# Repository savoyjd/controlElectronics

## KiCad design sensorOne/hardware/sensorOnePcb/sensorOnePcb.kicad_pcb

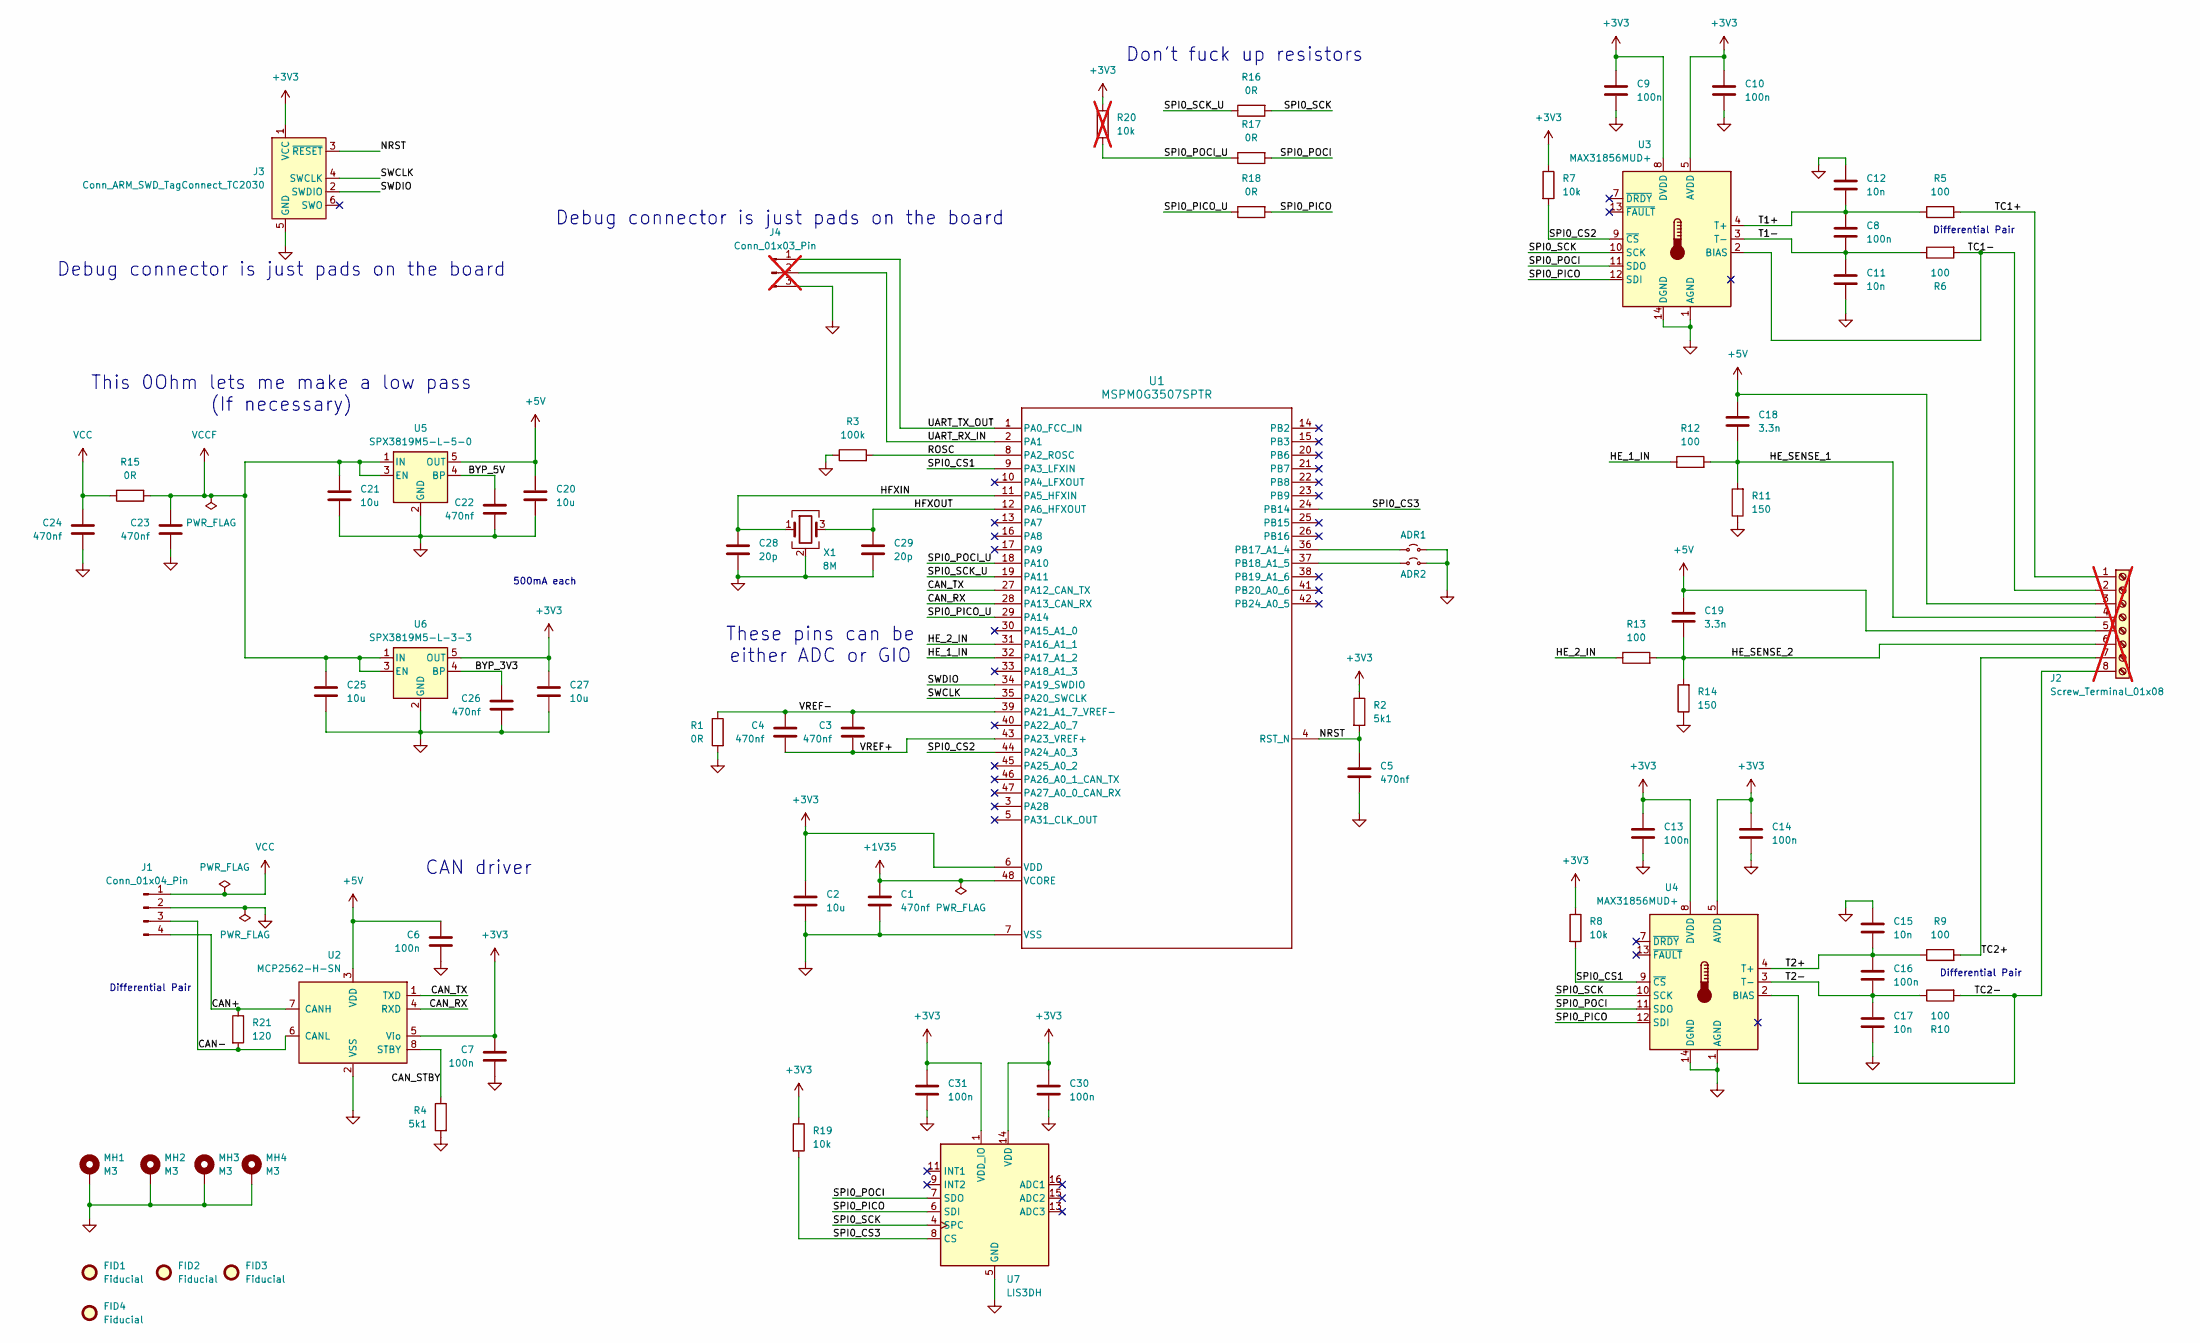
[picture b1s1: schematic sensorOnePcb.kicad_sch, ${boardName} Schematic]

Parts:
ADR1, ADR2: SolderJumper-2_P1.3mm_Open_RoundedPad1.0x1.5mm
C1, C3, C4, C5, C22, C23, C24, C26: 470nf; C_0603_1608Metric; Manufacturer Part Number CL10B474KA8NNNC; LCSC C1623
C2, C20, C21, C25, C27: 10u; C_0805_2012Metric; Manufacturer Part Number CL21A106KAYNNNE; LCSC C15850
C6, C7, C8, C9, C10, C13, C14, C16, C30, C31: 100n; C_0603_1608Metric; Manufacturer Part Number CC0603KRX7R9BB104; LCSC C14663
C11, C12, C15, C17: 10n; C_0603_1608Metric; Manufacturer Part Number 0603B103K500NT; LCSC C57112
C18, C19: 3.3n; C_0603_1608Metric; Manufacturer Part Number CL10B332KB8NNNC; LCSC C1613
C28, C29: 20p; C_0603_1608Metric; Manufacturer Part Number CL10C200JB8NNNC; LCSC C1648
FID1, FID2, FID3, FID4: Fiducial; Fiducial_1mm_Mask2mm
J1: Conn_01x04_Pin; JST_PH_B4B-PH-K_1x04_P2.00mm_Vertical; Manufacturer Part Number B4B-PH-K-S(LF)(SN); LCSC C131334
J2: Screw_Terminal_01x08; TerminalBlock_Xinya_XY308-2.54-8P_1x08_P2.54mm_Horizontal; not fitted
J3: Conn_ARM_SWD_TagConnect_TC2030; Tag-Connect_TC2030-IDC-FP_2x03_P1.27mm_Vertical
J4: Conn_01x03_Pin; PinHeader_1x03_P2.54mm_Vertical; not fitted
MH1, MH2, MH3, MH4: M3; MountingHole_3.2mm_M3_Pad_Via
R1, R15, R16, R17, R18: 0R; R_0603_1608Metric; Manufacturer Part Number 0603WAF0000T5E; LCSC C21189
R2, R4: 5k1; R_0603_1608Metric; Manufacturer Part Number 0603WAF5101T5E; LCSC C23186
R3: 100k; R_0603_1608Metric; Manufacturer Part Number ERA3AEB104V; LCSC C190609
R5, R6, R9, R10, R12, R13: 100; R_0603_1608Metric; Manufacturer Part Number 0603WAF1000T5E; LCSC C22775
R7, R8, R19: 10k; R_0603_1608Metric; Manufacturer Part Number 0603WAF1002T5E; LCSC C25804
R11, R14: 150; R_0603_1608Metric; Manufacturer Part Number 0603WAF1500T5E; LCSC C22808
R20: 10k; R_0603_1608Metric; Manufacturer Part Number 0603WAF1002T5E; LCSC C25804; not fitted
R21: 120; R_0603_1608Metric; Manufacturer Part Number 0603WAF1200T5E; LCSC C22787
U1: MSPM0G3507SPTR; PT0048A-IPC_A; Manufacturer Part Number MSPM0G3507SPTR; LCSC C22362630
U2: MCP2562-H-SN; SOIC-8_3.9x4.9mm_P1.27mm; Manufacturer Part Number MCP2562-H/SN; LCSC C635955
U3, U4: MAX31856MUD+; TSSOP-14_4.4x5mm_P0.65mm; Manufacturer Part Number MAX31856MUD+; LCSC C116632
U5: SPX3819M5-L-5-0; SOT-23-5; Manufacturer Part Number SPX3819M5-L-5-0/TR; LCSC C13417
U6: SPX3819M5-L-3-3; SOT-23-5; Manufacturer Part Number SPX3819M5-L-3-3/TR; LCSC C9055
U7: LIS3DH; LGA-16_3x3mm_P0.5mm_LayoutBorder3x5y; Manufacturer Part Number LIS3DHTR; LCSC C15134
X1: 8M; Crystal_SMD_3225-4Pin_3.2x2.5mm; Manufacturer Part Number SX3M8.000M20F30TNN; LCSC C2901556

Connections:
+1V35: C1.1, U1.48 (VCORE)
+3V3: C2.1, C7.1, C9.1, C10.1, C13.1, C14.1, C27.1, C30.1, C31.1, J3.1 (VCC), R2.1, R7.1, R8.1, R19.1, R20.1, U1.6 (VDD), U2.5 (Vio), U3.5 (AVDD), U3.8 (DVDD), U4.5 (AVDD), U4.8 (DVDD), U6.5 (OUT), U7.1 (VDD_IO), U7.14 (VDD)
+5V: C6.1, C18.1, C19.1, C20.1, J2.3, J2.5, U2.3 (VDD), U5.5 (OUT)
/BYP_3V3: C26.1, U6.4 (BP)
/BYP_5V: C22.1, U5.4 (BP)
/CAN+: J1.4, R21.1, U2.7 (CANH)
/CAN-: J1.3, R21.2, U2.6 (CANL)
/CAN_RX: U1.28 (PA13_CAN_RX), U2.4 (RXD)
/CAN_STBY: R4.1, U2.8 (STBY)
/CAN_TX: U1.27 (PA12_CAN_TX), U2.1 (TXD)
/HE_1_IN: R12.1, U1.32 (PA17_A1_2)
/HE_2_IN: R13.1, U1.31 (PA16_A1_1)
/HE_SENSE_1: C18.2, J2.4, R11.2, R12.2
/HE_SENSE_2: C19.2, J2.6, R13.2, R14.2
/HFXIN: C28.1, U1.11 (PA5_HFXIN), X1.1
/HFXOUT: C29.1, U1.12 (PA6_HFXOUT), X1.3
/NRST: C5.1, J3.3 (~RESET), R2.2, U1.4 (RST_N)
/ROSC: R3.2, U1.8 (PA2_ROSC)
/SPI0_CS1: R8.2, U1.9 (PA3_LFXIN), U4.9 (~CS)
/SPI0_CS2: R7.2, U1.44 (PA24_A0_3), U3.9 (~CS)
/SPI0_CS3: R19.2, U1.24 (PB14), U7.8 (CS)
/SPI0_PICO: R18.2, U3.12 (SDI), U4.12 (SDI), U7.6 (SDI)
/SPI0_PICO_U: R18.1, U1.29 (PA14)
/SPI0_POCI: R17.2, U3.11 (SDO), U4.11 (SDO), U7.7 (SDO)
/SPI0_POCI_U: R17.1, R20.2, U1.18 (PA10)
/SPI0_SCK: R16.2, U3.10 (SCK), U4.10 (SCK), U7.4 (SPC)
/SPI0_SCK_U: R16.1, U1.19 (PA11)
/SWCLK: J3.4 (SWCLK), U1.35 (PA20_SWCLK)
/SWDIO: J3.2 (SWDIO), U1.34 (PA19_SWDIO)
/T1+: C8.1, C12.2, R5.1, U3.4 (T+)
/T1-: C8.2, C11.1, R6.1, U3.3 (T-)
/T2+: C15.2, C16.1, R9.1, U4.4 (T+)
/T2-: C16.2, C17.1, R10.1, U4.3 (T-)
/TC1+: J2.1, R5.2
/TC1-: J2.2, R6.2, U3.2 (BIAS)
/TC2+: J2.7, R9.2
/TC2-: J2.8, R10.2, U4.2 (BIAS)
/UART_RX_IN: J4.2, U1.2 (PA1)
/UART_TX_OUT: J4.1, U1.1 (PA0_FCC_IN)
/VREF+: C3.2, C4.2, U1.43 (PA23_VREF+)
/VREF-: C3.1, C4.1, R1.1, U1.39 (PA21_A1_7_VREF-)
GND: ADR1.2 (B), ADR2.2 (B), C1.2, C2.2, C5.2, C6.2, C7.2, C9.2, C10.2, C11.2, C12.1, C13.2, C14.2, C15.1, C17.2, C20.2, C21.2, C22.2, C23.2, C24.2, C25.2, C26.2, C27.2, C28.2, C29.2, C30.2, C31.2, J1.2, J3.5 (GND), J4.3, MH1.1 (1_1), MH2.1 (1_1), MH3.1 (1_1), MH4.1 (1_1), R1.2, R3.1, R4.2, R11.1, R14.1, U1.7 (VSS), U2.2 (VSS), U3.1 (AGND), U3.14 (DGND), U4.1 (AGND), U4.14 (DGND), U5.2 (GND), U6.2 (GND), U7.5 (GND), U7.10 (GND), U7.12 (GND), X1.2 (G), X1.4 (G)
unnamed: ADR1.1 (A), U1.36 (PB17_A1_4)
unnamed: ADR2.1 (A), U1.37 (PB18_A1_5)
VCC: C24.1, J1.1, R15.1
VCCF: C21.1, C23.1, C25.1, R15.2, U5.1 (IN), U5.3 (EN), U6.1 (IN), U6.3 (EN)

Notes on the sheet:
Debug connector is just pads on the board
Differential Pair
500mA each
Don't fuck up resistors
These pins can be either ADC or GIO
CAN driver
This 0Ohm lets me make a low pass (If necessary)

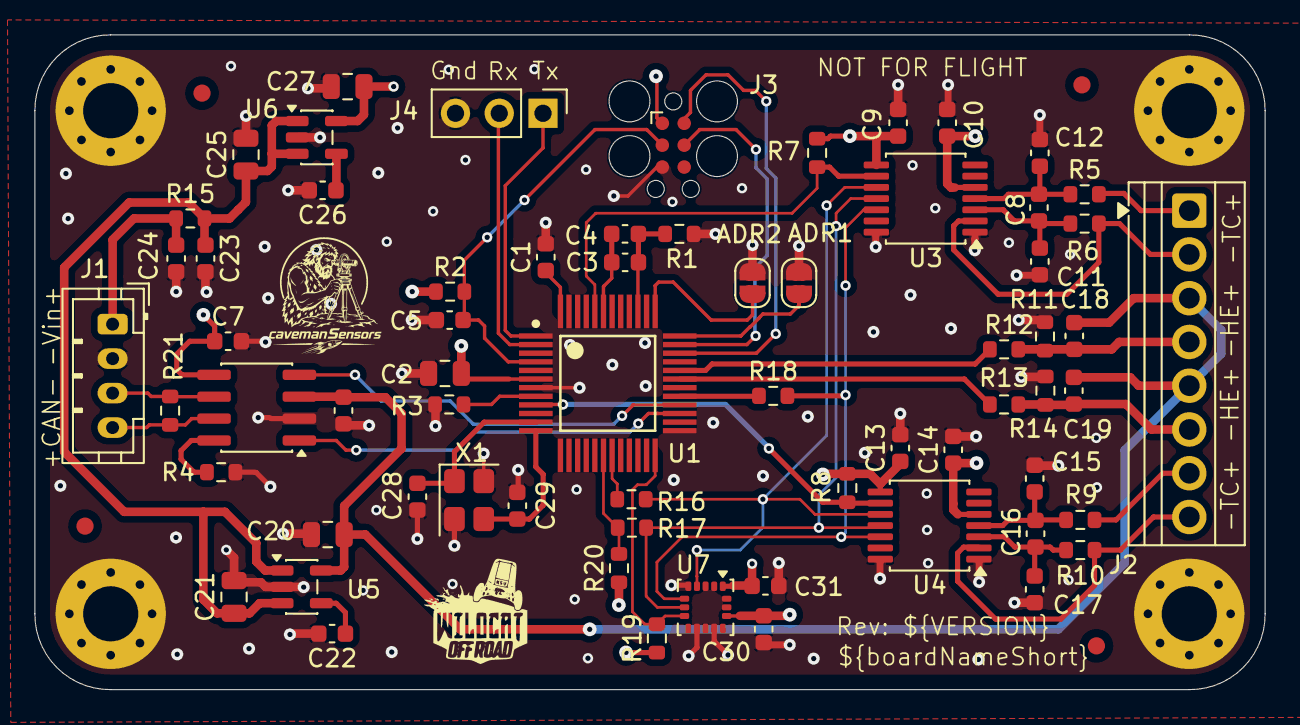
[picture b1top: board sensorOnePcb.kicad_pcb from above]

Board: 4 copper layers, 71.4 x 38.0 mm, 74 parts (0 on the bottom side), 46 nets.

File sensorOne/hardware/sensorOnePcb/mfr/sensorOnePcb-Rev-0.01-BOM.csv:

Designator,Quantity,DNP,Value,Footprint,Manufacturer,Manufacturer Part Number,,Distributor Link 1,Distributor Link 2,LCSC
"C1,C3,C4,C5,C22,C23,C24,C26",8,,470nf,Capacitor_SMD:C_0603_1608Metric,Samsung Electro-Mechanics,CL10B474KA8NNNC,,https://mou.sr/4dNlwD6,https://www.digikey.com/en/products/detail/samsung-electro-m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,C1623
"C2,C20,C21,C25,C27",5,,10u,Capacitor_SMD:C_0805_2012Metric,Samsung Electro-Mechanics,CL21A106KAYNNNE,,https://mou.sr/4uLKdaq,https://www.digikey.com/en/products/detail/samsung-electro-m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,C15850
"C6,C7,C8,C9,C10,C13,C14,C16,C30,C31",10,,100n,Capacitor_SMD:C_0603_1608Metric,YAGEO,CC0603KRX7R9BB104,,https://mou.sr/4nYrB47,https://www.digikey.com/en/products/detail/yageo/CC0603KRX7R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,C14663
"C11,C12,C15,C17",4,,10n,Capacitor_SMD:C_0603_1608Metric,FH (Guangdong Fenghua Advanced Tech),0603B103K500NT,,https://mou.sr/43Ixhpz,https://www.digikey.com/en/products/detail/knowles-novacap/0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,C57112
"C18,C19",2,,3.3n,Capacitor_SMD:C_0603_1608Metric,Samsung Electro-Mechanics,CL10B332KB8NNNC,,https://mou.sr/4tXYoaV,https://www.digikey.com/en/products/detail/samsung-electro-m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,C1613
"C28,C29",2,,20p,Capacitor_SMD:C_0603_1608Metric,Samsung Electro-Mechanics,CL10C200JB8NNNC,,https://mou.sr/49ZVefG,https://www.digikey.com/en/products/detail/samsung-electro-m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,C1648
J1,1,,Conn_01x04_Pin,Connector_JST:JST_PH_B4B-PH-K_1x04_P2.00mm_Vertical,JST,B4B-PH-K-S(LF)(SN),,https://mou.sr/3PHBmaw,https://www.digikey.com/en/products/detail/jst-sales-america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,C131334
"R1,R15,R16,R17,R18",5,,0R,Resistor_SMD:R_0603_1608Metric,UNI-ROYAL(Uniroyal Elec),0603WAF0000T5E,,https://mou.sr/4dUOUHE,https://www.tme.com/us/en-us/details/0603waf0000t5e/smd-resi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,C21189
"R2,R4",2,,5k1,Resistor_SMD:R_0603_1608Metric,UNI-ROYAL(Uniroyal Elec),0603WAF5101T5E,,https://mou.sr/4nVtD5j,https://www.tme.com/us/en-us/details/0603waf5101t5e/smd-resi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,C23186
R3,1,,100k,Resistor_SMD:R_0603_1608Metric,PANASONIC,ERA3AEB104V,,https://mou.sr/4fQ43MR,https://www.digikey.com/en/products/detail/panasonic-industr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,C190609
"R5,R6,R9,R10,R12,R13",6,,100,Resistor_SMD:R_0603_1608Metric,UNI-ROYAL(Uniroyal Elec),0603WAF1000T5E,,https://mou.sr/4vinUsC,https://www.tme.com/us/en-us/details/0603waf1000t5e/smd-resi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,C22775
"R7,R8,R19",3,,10k,Resistor_SMD:R_0603_1608Metric,UNI-ROYAL(Uniroyal Elec),0603WAF1002T5E,,https://mou.sr/4fgJ1qA,https://www.tme.com/us/en-us/details/0603waf1002t5e/smd-resi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,C25804
"R11,R14",2,,150,Resistor_SMD:R_0603_1608Metric,UNI-ROYAL(Uniroyal Elec),0603WAF1500T5E,,https://mou.sr/4x3bgzy,https://www.tme.com/us/en-us/details/0603waf1500t5e/smd-resi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,C22808
R20,1,DNP,10k,Resistor_SMD:R_0603_1608Metric,UNI-ROYAL(Uniroyal Elec),0603WAF1002T5E,,https://mou.sr/4fgJ1qA,https://www.tme.com/us/en-us/details/0603waf1002t5e/smd-resi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,C25804
R21,1,,120,Resistor_SMD:R_0603_1608Metric,UNI-ROYAL(Uniroyal Elec),0603WAF1200T5E,,https://mou.sr/4dNJZIl,https://www.tme.com/us/en-us/details/0603waf1200t5e/smd-resi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,C22787
U1,1,,MSPM0G3507SPTR,MSPM0:PT0048A-IPC_A,Texas Instruments,MSPM0G3507SPTR,,https://mou.sr/4akP21Z,https://www.digikey.com/en/products/detail/texas-instruments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,C22362630
U2,1,,MCP2562-H-SN,Package_SO:SOIC-8_3.9x4.9mm_P1.27mm,Microchip Tech,MCP2562-H/SN,,https://mou.sr/4uKPH56,https://www.digikey.com/en/products/detail/microchip-technol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,C635955
"U3,U4",2,,MAX31856MUD+,Package_SO:TSSOP-14_4.4x5mm_P0.65mm,Analog Devices Inc./Maxim Integrated,MAX31856MUD+,,https://mou.sr/3RT1kbw,https://www.digikey.com/en/products/detail/analog-devices-in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,C116632
U5,1,,SPX3819M5-L-5-0,Package_TO_SOT_SMD:SOT-23-5,MaxLinear,SPX3819M5-L-5-0/TR,,https://mou.sr/49u98qg,https://www.digikey.com/en/products/detail/maxlinear-inc/SPX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,C13417
U6,1,,SPX3819M5-L-3-3,Package_TO_SOT_SMD:SOT-23-5,MaxLinear,SPX3819M5-L-3-3/TR,,https://mou.sr/4dJ23Dm,https://www.digikey.com/en/products/detail/maxlinear-inc/SPX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,C9055
U7,1,,LIS3DH,Package_LGA:LGA-16_3x3mm_P0.5mm_LayoutBorder3x5y,STMicroelectronics,LIS3DHTR,,https://mou.sr/4xdHCHU,https://www.digikey.com/en/products/detail/stmicroelectronic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,C15134
X1,1,,8M,Crystal:Crystal_SMD_3225-4Pin_3.2x2.5mm,Shenzhen SCTF Elec,SX3M8.000M20F30TNN,,,https://www.digikey.com/en/products/detail/shenzhen-sctf-ele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,C2901556

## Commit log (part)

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2026-05-28 sensorOne initial baseline
2026-05-30 PCB cleanup
2026-06-06 main connector now 2mm jst, added package details
2026-06-07 pcb clean up
